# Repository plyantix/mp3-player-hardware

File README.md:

# MiniMusicBox

An open source, RP2350 based MP3 player, with LiPo battery charging, USB-C, MicroSD storage, high fidelity analog audio, and a black & white LCD screen.

Although this version of the project will work, I would not recommend building it, as it has a design flaw leading to high idle battery consumption. This will be fixed in a future revision.

This board was designed with the manufacturing tolerances of [JLCPCB](https://jlcpcb.com/) in mind.

(Incomplete) firmware [here](https://github.com/plyantix/mp3-project-software).

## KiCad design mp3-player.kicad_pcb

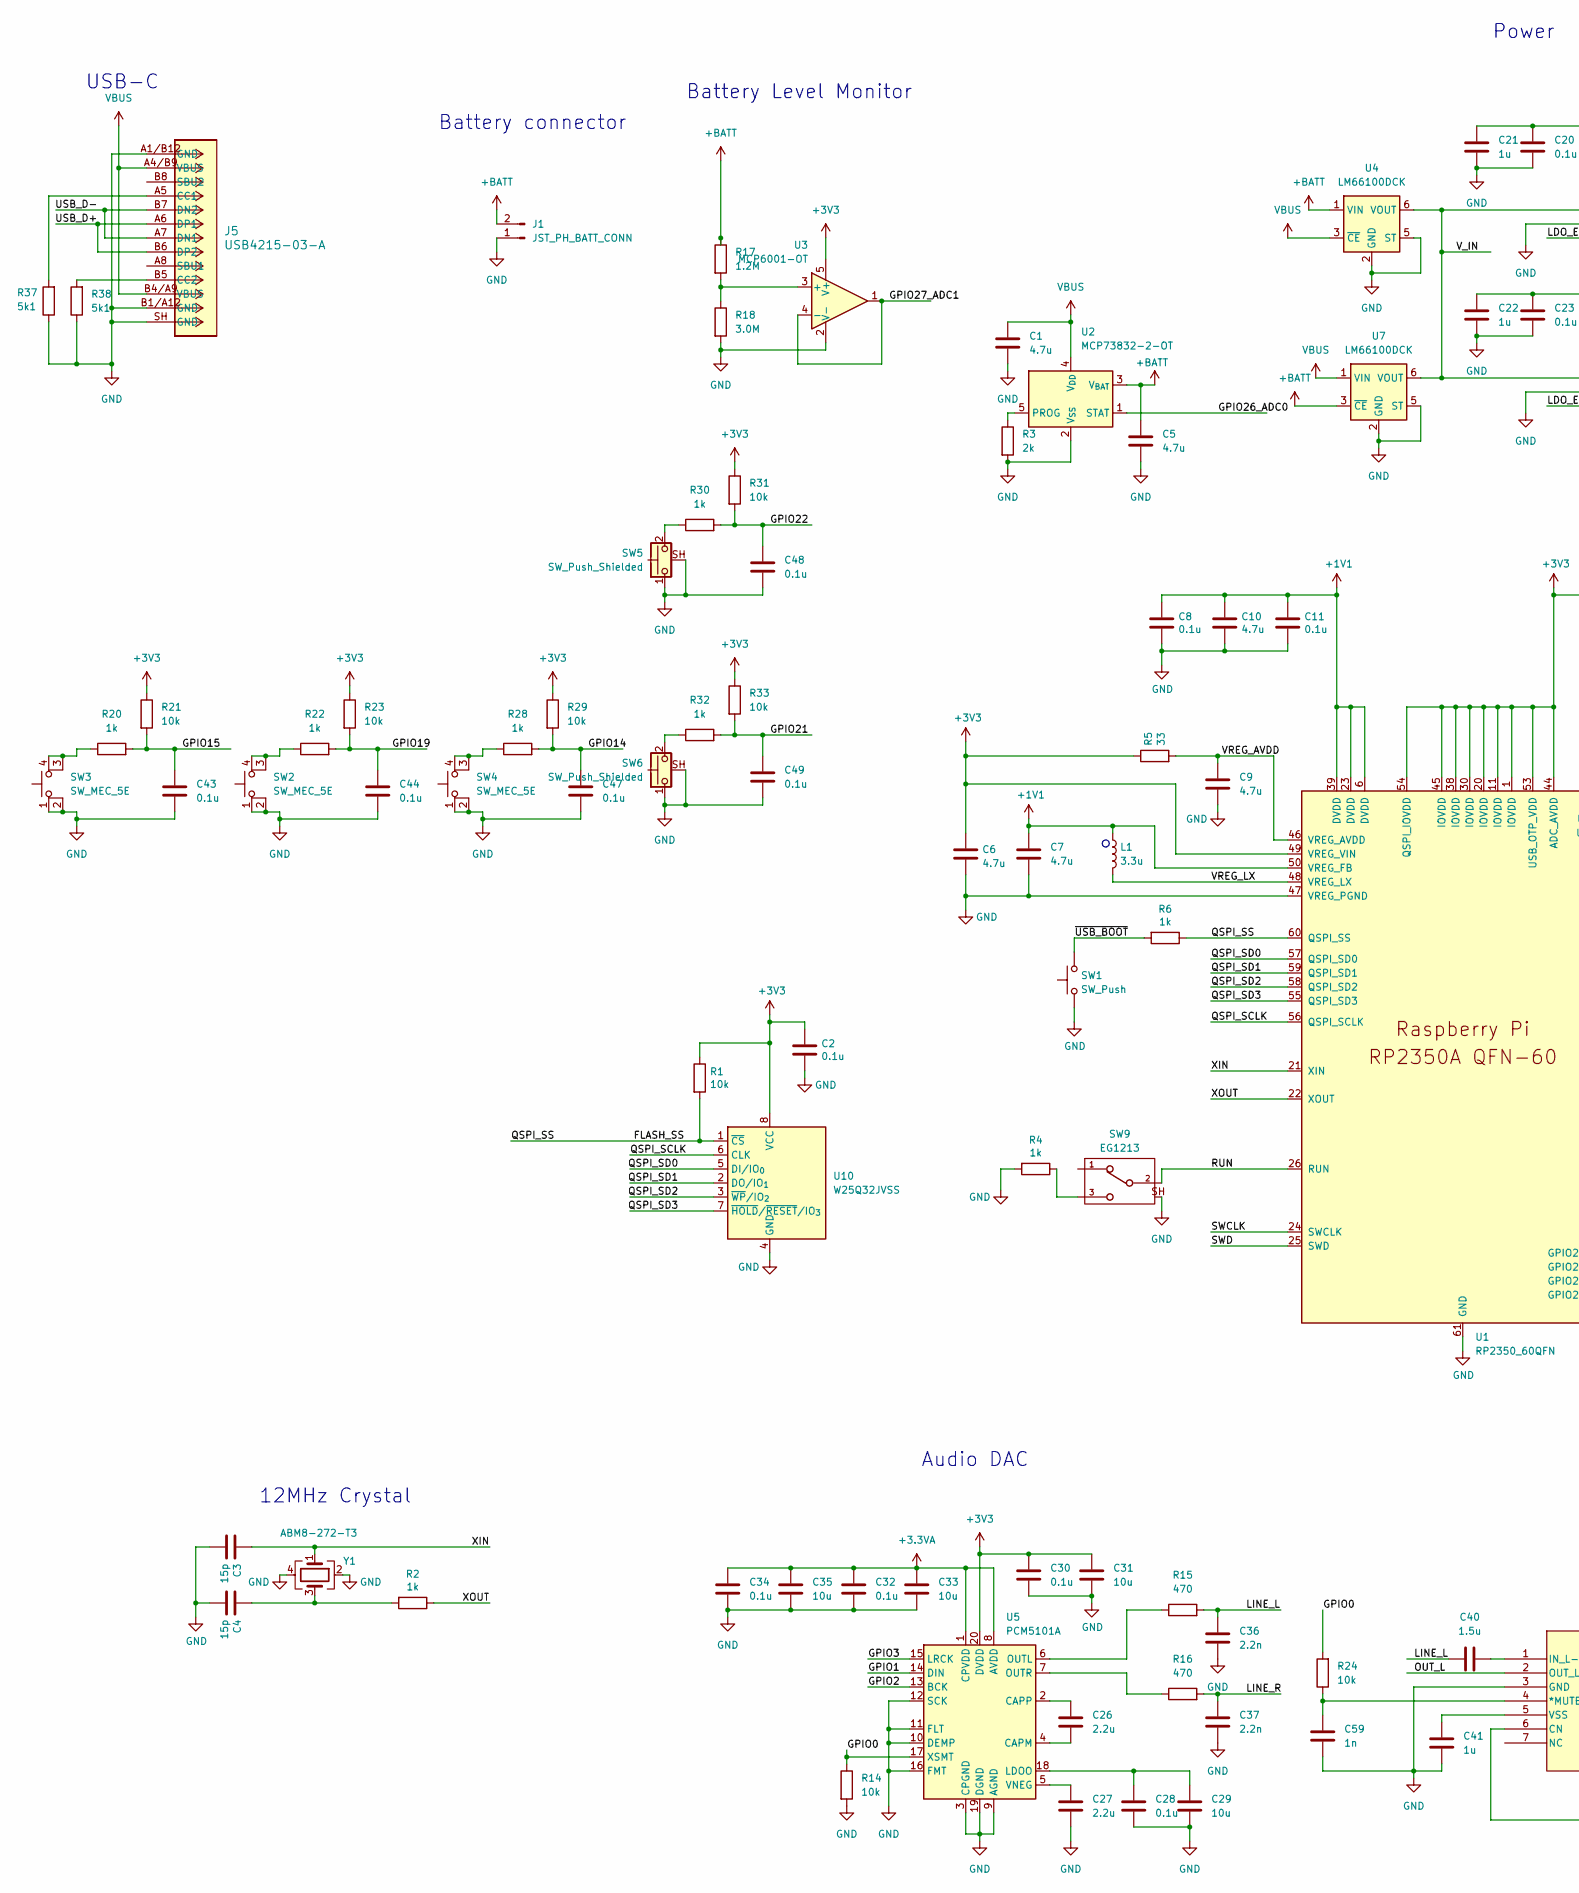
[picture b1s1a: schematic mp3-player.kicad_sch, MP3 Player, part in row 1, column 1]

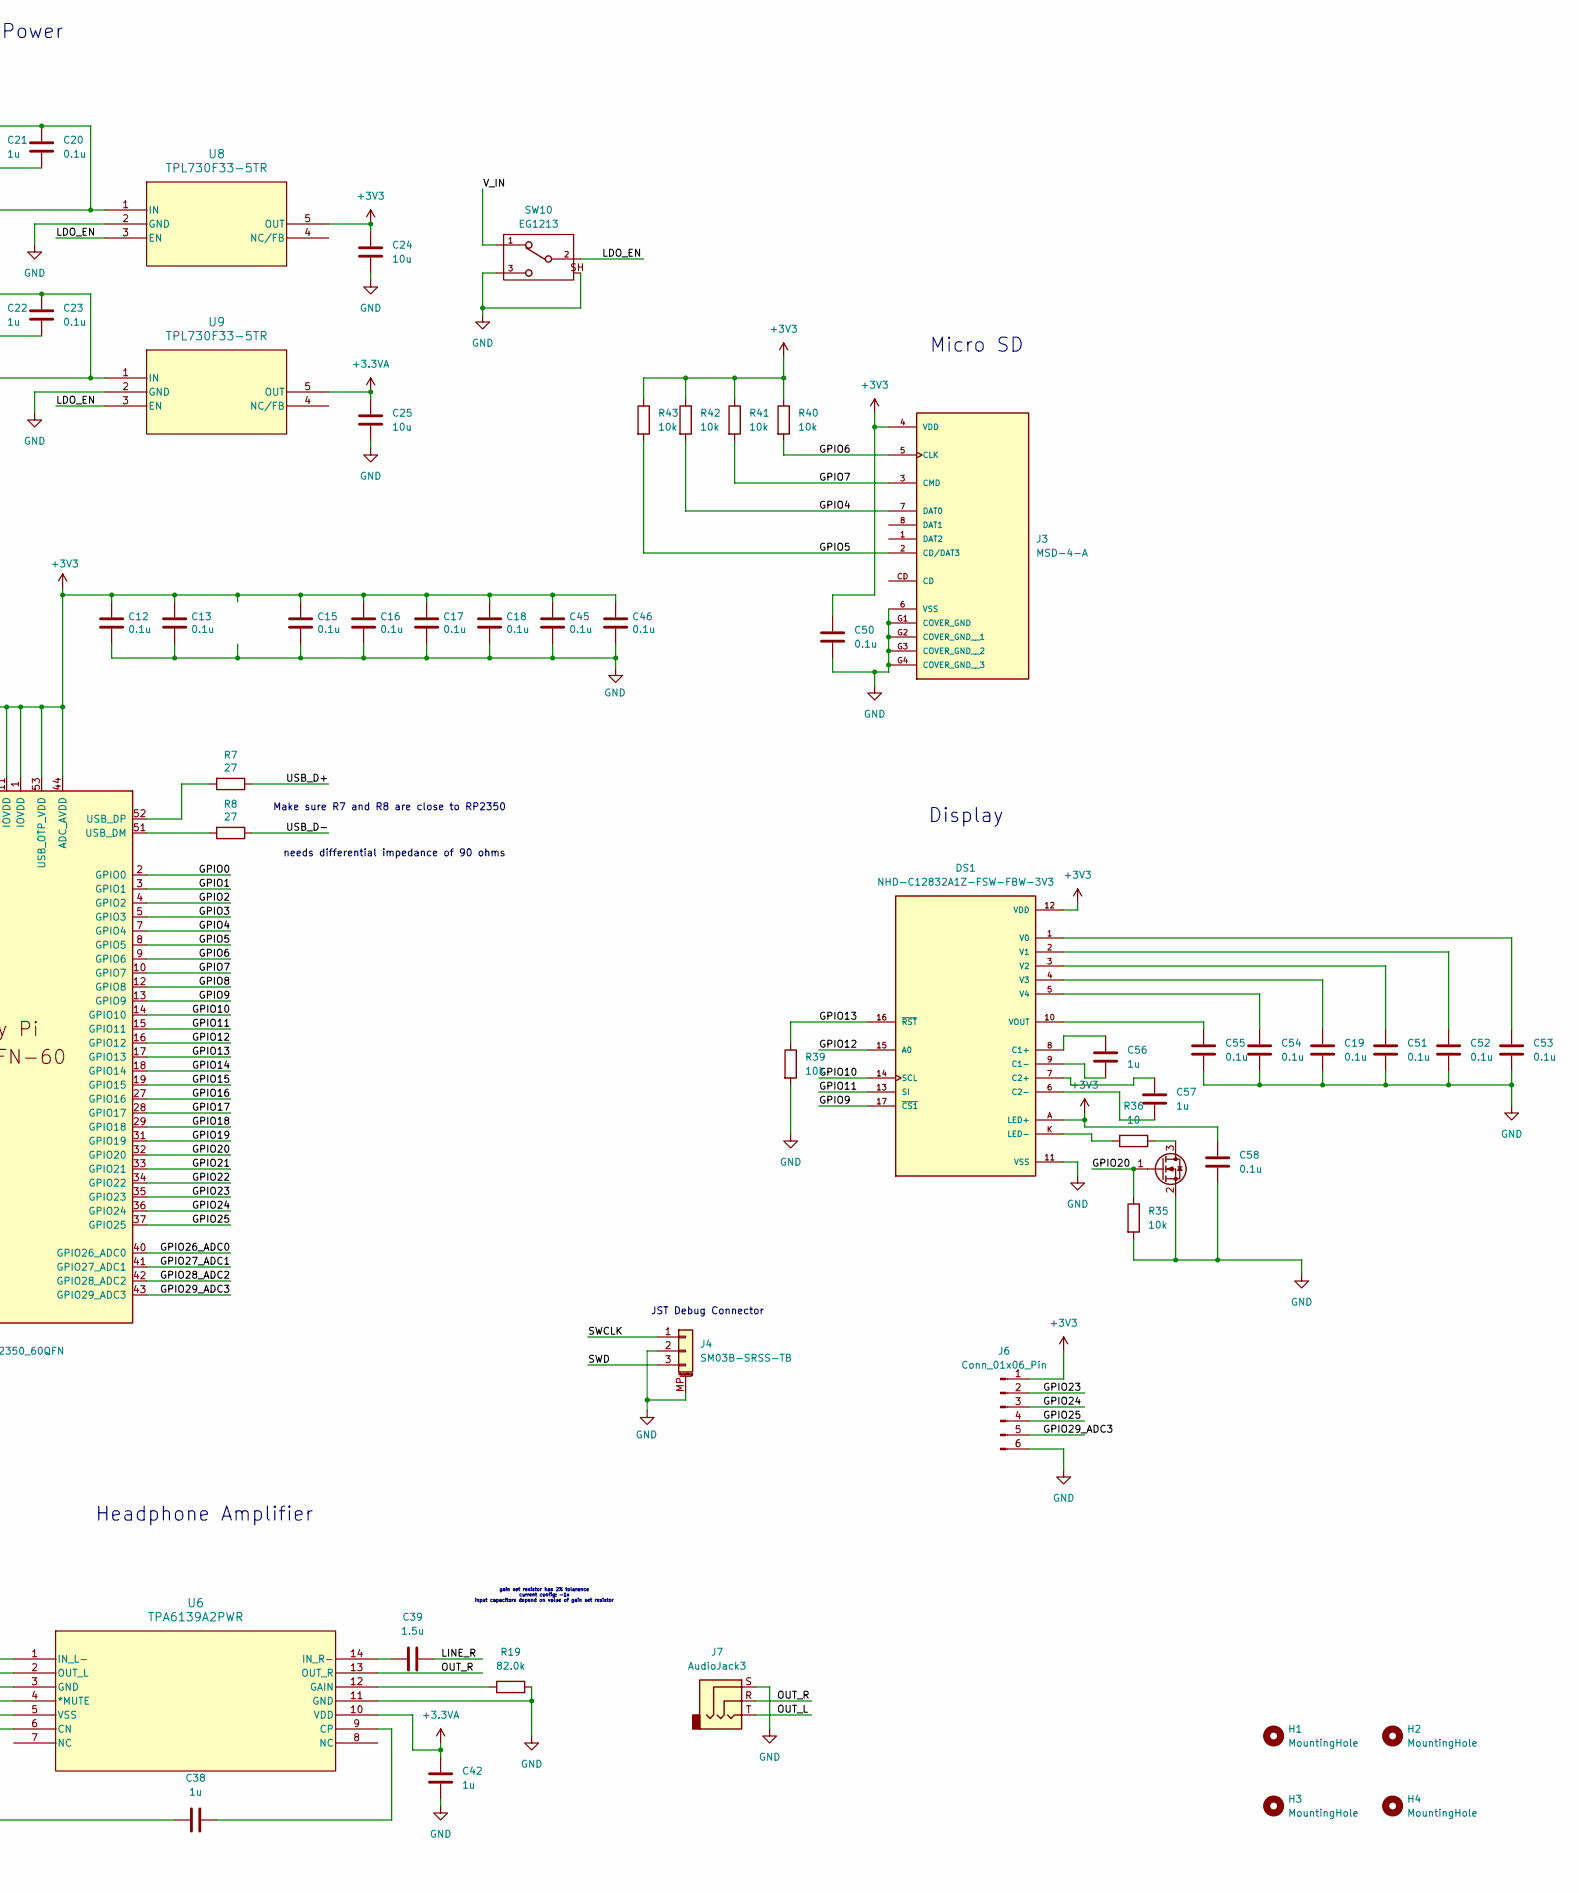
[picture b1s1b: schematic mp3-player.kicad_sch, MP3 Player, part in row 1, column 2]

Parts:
C1, C5, C9, C10: 4.7u; C_0402_1005Metric_NoSilk
C2, C8, C11, C12, C13, C15, C16, C17, C18, C19, C20, C23, C28, C30, C32, C34, C43, C44, C45, C46, C47, C48, C49, C50, C51, C52, C53, C54, C55, C58: 0.1u; C_0402_1005Metric_NoSilk
C3, C4: 15p; C_0402_1005Metric_NoSilk
C6, C7: 4.7u; C_0402_1005Metric_small_pads
C21, C22, C38, C41, C42, C56, C57: 1u; C_0402_1005Metric_NoSilk
C24, C25, C29, C31, C33, C35: 10u; C_0402_1005Metric_NoSilk
C26, C27: 2.2u; C_0402_1005Metric_NoSilk
C36, C37: 2.2n; C_0402_1005Metric_NoSilk
C39, C40: 1.5u; C_0402_1005Metric_NoSilk
C59: 1n; C_0402_1005Metric_NoSilk
DS1: NHD-C12832A1Z-FSW-FBW-3V3; LCD_NHD-C12832A1Z-FSW-FBW-3V3; PARTREV 7
H1, H2, H3, H4: MountingHole; MountingHole_3.2mm_M3
J1: JST_PH_BATT_CONN; JST_PH_S2B-PH-K_1x02_P2.00mm_Horizontal
J3: MSD-4-A; CUI_MSD-4-A; PARTREV 1.0
J4: SM03B-SRSS-TB; JST_SH_SM03B-SRSS-TB_1x03-1MP_P1.00mm_Horizontal
J5: USB4215-03-A; CONN_8p94X6p5X3p16_12L_GCC
J6: Conn_01x06_Pin; PinHeader_1x06_P1.00mm_Vertical
J7: AudioJack3; KYCON_STX-3000
L1: 3.3u; L_pol_2016
Q2: 2N7002; SOT-23
R1, R14, R21, R23, R24, R29, R31, R33, R35, R39, R40, R41, R42, R43: 10k; R_0402_1005Metric_NoSilk
R2, R4, R6, R20, R22, R28, R30, R32: 1k; R_0402_1005Metric_NoSilk
R3: 2k; R_0402_1005Metric_NoSilk
R5: 33; R_0402_1005Metric_NoSilk
R7, R8: 27; R_0402_1005Metric_NoSilk
R15, R16: 470; R_0402_1005Metric_NoSilk
R17: 1.2M; R_0402_1005Metric_NoSilk
R18: 3.0M; R_0402_1005Metric_NoSilk
R19: 82.0k; R_0402_1005Metric_NoSilk
R36: 10; R_0402_1005Metric_NoSilk
R37, R38: 5k1; R_0402_1005Metric_NoSilk
SW1: SW_Push; SW_Push_1P1T_NO_Vertical_Wuerth_434133025816
SW2, SW3, SW4: SW_MEC_5E; SW4_1825910-B_TEC
SW5, SW6: SW_Push_Shielded; SW2_1825027-A_TEC
SW9, SW10: EG1213; OS102011MA1QN1_CNK
U1: RP2350_60QFN; RP2350-QFN-60-1EP_7x7_P0.4mm_EP3.4x3.4mm_ThermalVias
U2: MCP73832-2-OT; SOT-23-5
U3: MCP6001-OT; SOT-23-5
U4, U7: LM66100DCK; SOT-363_SC-70-6
U5: PCM5101A; TSSOP-20_4.4x6.5mm_P0.65mm
U6: TPA6139A2PWR; PW14
U8, U9: TPL730F33-5TR; SOT23-5-A_TPK
U10: W25Q32JVSS; SOIC-8_5.3x5.3mm_P1.27mm
Y1: ABM8-272-T3; Crystal_SMD_3225-4Pin_3.2x2.5mm

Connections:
+1V1: C7.1, C8.1, C10.1, C11.1, L1.1, U1.6 (DVDD), U1.23 (DVDD), U1.39 (DVDD), U1.50 (VREG_FB)
+3.3VA: C25.1, C32.1, C33.1, C34.1, C35.1, C42.1, U5.1 (CPVDD), U5.8 (AVDD), U6.10 (VDD), U9.5 (OUT)
+3V3: C2.1, C6.1, C12.1, C13.1, C15.1, C16.1, C17.1, C18.1, C24.1, C30.1, C31.1, C45.1, C46.1, C50.1, C58.1, DS1.12 (VDD), DS1.A (LED+), J3.4 (VDD), J6.1, R1.1, R5.1, R21.1, R23.1, R29.1, R31.1, R33.1, R40.1, R41.1, R42.1, R43.1, U1.1 (IOVDD), U1.11 (IOVDD), U1.20 (IOVDD), U1.30 (IOVDD), U1.38 (IOVDD), U1.44 (ADC_AVDD), U1.45 (IOVDD), U1.49 (VREG_VIN), U1.53 (USB_OTP_VDD), U1.54 (QSPI_IOVDD), U3.5 (V+), U5.20 (DVDD), U8.5 (OUT), U10.8 (VCC)
+BATT: C5.1, J1.2, R17.1, U2.3 (V_{BAT}), U4.1 (VIN), U7.3 (~CE)
/FLASH_SS: R1.2, R6.1, U1.60 (QSPI_SS), U10.1 (~CS)
/GPIO0: R14.1, R24.2, U1.2 (GPIO0), U5.17 (XSMT)
/GPIO1: U1.3 (GPIO1), U5.14 (DIN)
/GPIO2: U1.4 (GPIO2), U5.13 (BCK)
/GPIO3: U1.5 (GPIO3), U5.15 (LRCK)
/GPIO4: J3.7 (DAT0), R42.2, U1.7 (GPIO4)
/GPIO5: J3.2 (CD/DAT3), R43.2, U1.8 (GPIO5)
/GPIO6: J3.5 (CLK), R40.2, U1.9 (GPIO6)
/GPIO7: J3.3 (CMD), R41.2, U1.10 (GPIO7)
/GPIO8: U1.12 (GPIO8)
/GPIO9: DS1.17 (~CS1), U1.13 (GPIO9)
/GPIO10: DS1.14 (SCL), U1.14 (GPIO10)
/GPIO11: DS1.13 (SI), U1.15 (GPIO11)
/GPIO12: DS1.15 (A0), U1.16 (GPIO12)
/GPIO13: DS1.16 (~RST), R39.1, U1.17 (GPIO13)
/GPIO14: C47.1, R28.2, R29.2, U1.18 (GPIO14)
/GPIO15: C43.1, R20.2, R21.2, U1.19 (GPIO15)
/GPIO16: U1.27 (GPIO16)
/GPIO17: U1.28 (GPIO17)
/GPIO18: U1.29 (GPIO18)
/GPIO19: C44.1, R22.2, R23.2, U1.31 (GPIO19)
/GPIO20: Q2.1 (G), R35.1, U1.32 (GPIO20)
/GPIO21: C49.1, R32.2, R33.2, U1.33 (GPIO21)
/GPIO22: C48.1, R30.2, R31.2, U1.34 (GPIO22)
/GPIO23: J6.2, U1.35 (GPIO23)
/GPIO24: J6.3, U1.36 (GPIO24)
/GPIO25: J6.4, U1.37 (GPIO25)
/GPIO26_ADC0: U1.40 (GPIO26_ADC0), U2.1 (STAT)
/GPIO27_ADC1: U1.41 (GPIO27_ADC1), U3.1, U3.4 (-)
/GPIO28_ADC2: U1.42 (GPIO28_ADC2)
/GPIO29_ADC3: J6.5, U1.43 (GPIO29_ADC3)
/LINE_L: C36.1, C40.1, R15.2
/LINE_R: C37.1, C39.2, R16.2
/OUT_L: J7.T, U6.2 (OUT_L)
/OUT_R: J7.R, U6.13 (OUT_R)
/QSPI_SCLK: U1.56 (QSPI_SCLK), U10.6 (CLK)
/QSPI_SD0: U1.57 (QSPI_SD0), U10.5 (DI/IO_{0})
/QSPI_SD1: U1.59 (QSPI_SD1), U10.2 (DO/IO_{1})
/QSPI_SD2: U1.58 (QSPI_SD2), U10.3 (~WP/IO_{2})
/QSPI_SD3: U1.55 (QSPI_SD3), U10.7 (~HOLD/~RESET/IO_{3})
/RUN: SW9.2, U1.26 (RUN)
/SWCLK: J4.1, U1.24 (SWCLK); also elsewhere on the board
/SWD: J4.3, U1.25 (SWD); also elsewhere on the board
/USB_D+: J5.A6 (DP1), J5.B6 (DP2), R7.1
/USB_D-: J5.A7 (DN1), J5.B7 (DN2), R8.1
/VREG_AVDD: C9.1, R5.2, U1.46 (VREG_AVDD)
/VREG_LX: L1.2, U1.48 (VREG_LX)
/XIN: C3.1, U1.21 (XIN), Y1.1
/XOUT: R2.1, U1.22 (XOUT)
/~USB_BOOT: R6.2, SW1.2; also elsewhere on the board
GND: C1.2, C2.2, C3.2, C4.2, C5.2, C6.2, C7.2, C8.2, C9.2, C10.2, C11.2, C12.2, C13.2, C15.2, C16.2, C17.2, C18.2, C19.2, C20.2, C21.2, C22.2, C23.2, C24.2, C25.2, C27.2, C28.2, C29.2, C30.2, C31.2, C32.2, C33.2, C34.2, C35.2, C36.2, C37.2, C41.1, C42.2, C43.2, C44.2, C45.2, C46.2, C47.2, C48.2, C49.2, C50.2, C51.2, C52.2, C53.2, C54.2, C55.2, C58.2, C59.1, DS1.11 (VSS), J1.1, J3.6 (VSS), J3.G1 (COVER_GND), J3.G2 (COVER_GND__1), J3.G3 (COVER_GND__2), J3.G4 (COVER_GND__3), J4.2, J4.MP (MountPin), J5.A1/B12 (GND), J5.B1/A12 (GND), J5.SH (GND), J6.6, J7.S, Q2.2 (S), R3.2, R4.2, R14.2, R18.2, R19.2, R35.2, R37.1, R38.1, R39.2, SW1.1, SW2.1, SW2.2, SW3.1, SW3.2, SW4.1, SW4.2, SW5.1, SW5.SH (B), SW6.1, SW6.SH (B), SW9.SH, SW10.3, SW10.SH, U1.47 (VREG_PGND), U1.61 (GND), U2.2 (V_{SS}), U3.2 (V-), U4.2 (GND), U4.5 (ST), U5.3 (CPGND), U5.9 (AGND), U5.10 (DEMP), U5.11 (FLT), U5.12 (SCK), U5.16 (FMT), U5.19 (DGND), U6.3 (GND), U6.11 (GND), U7.2 (GND), U7.5 (ST), U8.2 (GND), U9.2 (GND), U10.4 (GND), Y1.2, Y1.4; also elsewhere on the board
unnamed: C4.1, R2.2, Y1.3
unnamed: C56.2, DS1.8 (C1+)
unnamed: C56.1, DS1.9 (C1-)
unnamed: C57.2, DS1.7 (C2+)
unnamed: C57.1, DS1.6 (C2-)
unnamed: DS1.K (LED-), R36.2
unnamed: C53.1, DS1.1 (V0)
unnamed: C52.1, DS1.2 (V1)
unnamed: C51.1, DS1.3 (V2)
unnamed: C19.1, DS1.4 (V3)
unnamed: C54.1, DS1.5 (V4)
unnamed: C55.1, DS1.10 (VOUT)
unnamed: J5.A5 (CC1), R37.2
unnamed: J5.B5 (CC2), R38.2
unnamed: Q2.3 (D), R36.1
unnamed: R4.1, SW9.3
unnamed: R30.1, SW5.2
unnamed: R32.1, SW6.2
unnamed: R22.1, SW2.3 (K), SW2.4 (A)
unnamed: R20.1, SW3.3 (K), SW3.4 (A)
unnamed: R28.1, SW4.3 (K), SW4.4 (A)
unnamed: R8.2, U1.51 (USB_DM)
unnamed: R7.2, U1.52 (USB_DP)
unnamed: R3.1, U2.5 (PROG)
unnamed: R17.2, R18.1, U3.3 (+)
unnamed: C26.2, U5.4 (CAPM)
unnamed: C26.1, U5.2 (CAPP)
unnamed: C28.1, C29.1, U5.18 (LDOO)
unnamed: R15.1, U5.6 (OUTL)
unnamed: R16.1, U5.7 (OUTR)
unnamed: C27.1, U5.5 (VNEG)
unnamed: C59.2, R24.1, U6.4 (*MUTE)
unnamed: C38.2, U6.6 (CN)
unnamed: C38.1, U6.9 (CP)
unnamed: R19.1, U6.12 (GAIN)
unnamed: C40.2, U6.1 (IN_L-)
unnamed: C39.1, U6.14 (IN_R-)
unnamed: C41.2, U6.5 (VSS)
VBUS: C1.1, J5.A4/B9 (VBUS), J5.B4/A9 (VBUS), U2.4 (V_{DD}), U4.3 (~CE), U7.1 (VIN)

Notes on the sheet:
USB-C
Battery connector
Micro SD
Power
12MHz Crystal
needs differential impedance of 90 ohms
Battery Level Monitor
JST Debug Connector
Audio DAC
gain set resistor has 2% tolarance current config: -1x input capacitors depend on value of gain set resistor
Make sure R7 and R8 are close to RP2350
Display
Headphone Amplifier

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
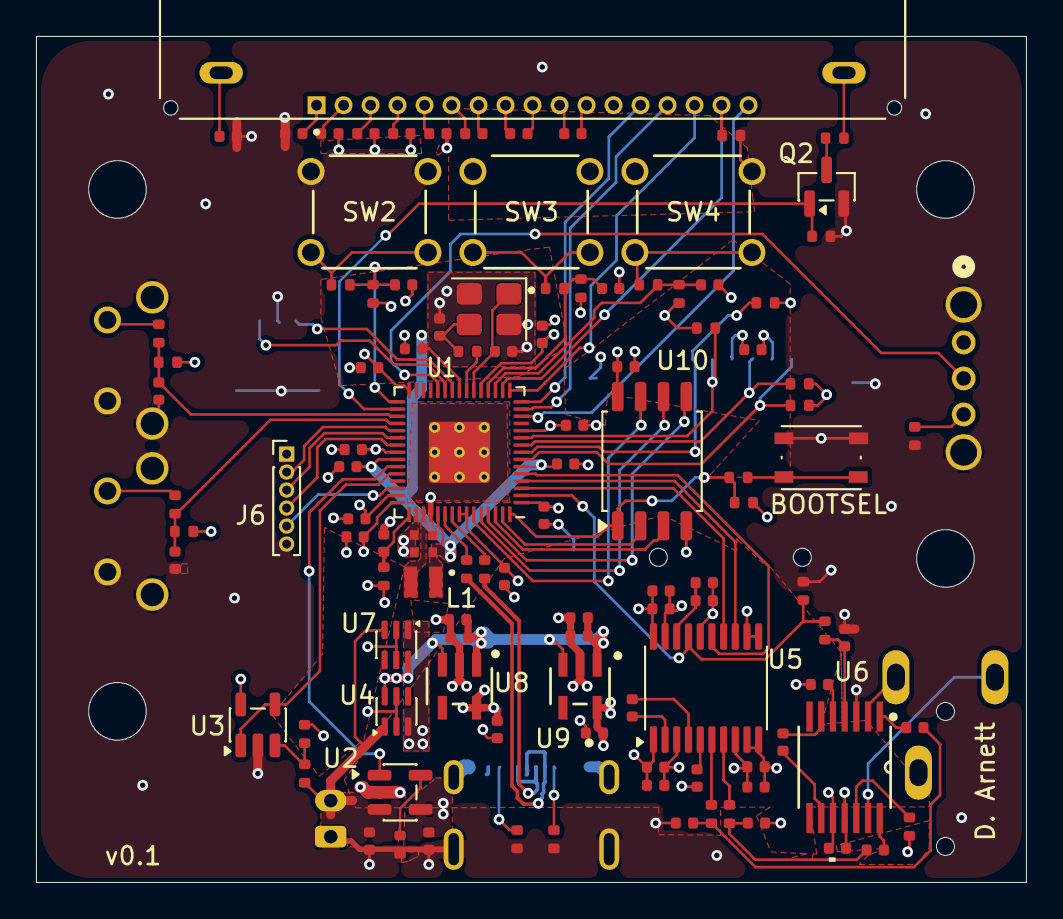
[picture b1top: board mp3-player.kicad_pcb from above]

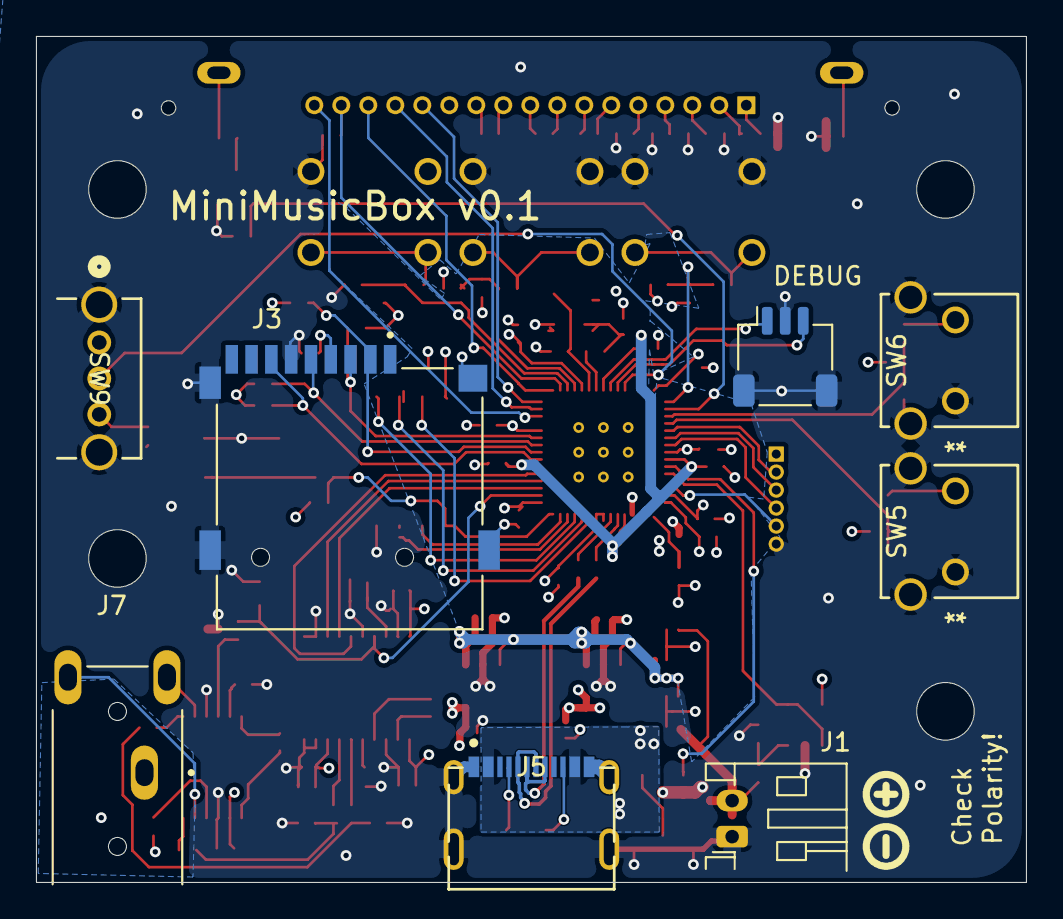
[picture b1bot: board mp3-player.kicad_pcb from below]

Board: 4 copper layers, 55.0 x 47.0 mm, 123 parts (8 on the bottom side), 90 nets.

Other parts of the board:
BOOTSEL: SW_Push; SW_Push_1P1T_NO_Vertical_Wuerth_434133025816
DEBUG: SM03B-SRSS-TB; JST_SH_SM03B-SRSS-TB_1x03-1MP_P1.00mm_Horizontal

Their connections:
/SWCLK: DEBUG.1; also elsewhere on the board
/SWD: DEBUG.3; also elsewhere on the board
/~USB_BOOT: BOOTSEL.2; also elsewhere on the board
GND: BOOTSEL.1, DEBUG.2, DEBUG.MP (MountPin); also elsewhere on the board

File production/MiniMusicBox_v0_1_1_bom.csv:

Designator,Footprint,Quantity,Value,LCSC Part #
BOOTSEL,SW_Push_1P1T_NO_Vertical_Wuerth_434133025816,1,SW_Push,
"C1, C10, C5, C6, C7, C9",0402,6,4.7u,
"C11, C12, C13, C15, C16, C17, C18, C19, C2, C20, C23, C28, C30, C32, C34, C43, C44, C45, C46, C47, C48, C49, C50, C51, C52, C53, C54, C55, C58, C8",0402,30,0.1u,
"C21, C22, C38, C41, C42, C56, C57",0402,7,1u,
"C24, C25, C29, C31, C33, C35",0402,6,10u,
"C26, C27",0402,2,2.2u,
"C3, C4",0402,2,15p,
"C36, C37",0402,2,2.2n,
"C39, C40",0402,2,1.5u,
C59,0402,1,1n,
J1,JST_PH_S2B-PH-K_1x02_P2.00mm_Horizontal,1,JST_PH_BATT_CONN,
L1,L_pol_2016,1,3.3u,
Q2,SOT-23,1,2N7002,
"R1, R14, R21, R23, R24, R29, R31, R33, R35, R39, R40, R41, R42, R43",0402,14,10k,
"R15, R16",0402,2,470,
R17,0402,1,1.2M,
R18,0402,1,3.0M,
R19,0402,1,82.0k,
"R2, R20, R22, R28, R30, R32, R4, R6",0402,8,1k,
R3,0402,1,2k,
R36,0402,1,10,
"R37, R38",0402,2,5k1,
R5,0402,1,33,
"R7, R8",0402,2,27,
U1,RP2350-QFN-60-1EP_7x7_P0.4mm_EP3.4x3.4mm_ThermalVias,1,RP2350_60QFN,
U10,SOIC-8_5.3x5.3mm_P1.27mm,1,W25Q32JVSS,
U2,SOT-23-5,1,MCP73832-2-OT,
U3,SOT-23-5,1,MCP6001-OT,
"U4, U7",SOT-363_SC-70-6,2,LM66100DCK,
U5,TSSOP-20_4.4x6.5mm_P0.65mm,1,PCM5101A,
U6,PW14,1,TPA6139A2PWR,
"U8, U9",SOT23-5-A_TPK,2,TPL730F33-5TR,
Y1,Crystal_SMD_3225-4Pin_3.2x2.5mm,1,ABM8-272-T3,

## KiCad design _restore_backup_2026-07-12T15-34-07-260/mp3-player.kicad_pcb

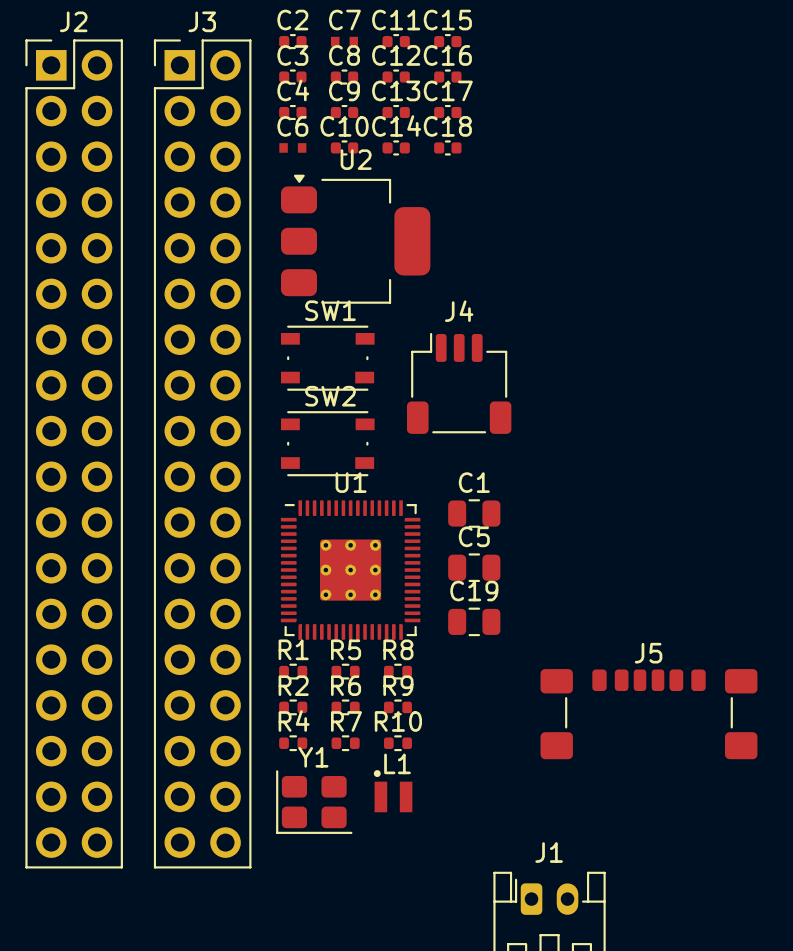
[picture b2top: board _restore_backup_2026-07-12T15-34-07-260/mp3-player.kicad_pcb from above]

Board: 2 copper layers, 39 parts (0 on the bottom side), 48 nets, no tracks yet.

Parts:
C1, C5, C19: 10u; C_0805_2012Metric
C2, C8, C11, C12, C13, C14, C15, C16, C17, C18: 100n; C_0402_1005Metric
C3, C4: 15p; C_0402_1005Metric
C6, C7: 4.7u; C_0402_1005Metric_small_pads
C9, C10: 4.7u; C_0402_1005Metric
J1: Conn_01x02; JST_PH_S2B-PH-K_1x02_P2.00mm_Horizontal
J2, J3: Conn_02x18_Odd_Even; PinHeader_2x18_P2.54mm_Vertical
J4: SM03B-SRSS-TB; JST_SH_SM03B-SRSS-TB_1x03-1MP_P1.00mm_Horizontal
J5: USB_C_Receptacle_USB2.0_14P; USB_C_Receptacle_GCT_USB4135-GF-A_6P_TopMnt_Horizontal
L1: 3.3u; L_pol_2016
R1, R9: DNF; R_0402_1005Metric
R2, R4, R6: 1k; R_0402_1005Metric
R5: 33; R_0402_1005Metric
R7, R8: 27; R_0402_1005Metric
R10: 0; R_0402_1005Metric
SW1, SW2: SW_Push; SW_Push_1P1T_NO_Vertical_Wuerth_434133025816
U1: RP2350_60QFN; RP2350-QFN-60-1EP_7x7_P0.4mm_EP3.4x3.4mm_ThermalVias
U2: NCP1117-3.3_SOT223; SOT-223-3_TabPin2
Y1: ABM8-272-T3; Crystal_SMD_3225-4Pin_3.2x2.5mm

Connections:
+1V1: C7.1, C8.1, C10.1, C11.1, L1.1, U1.6 (DVDD), U1.23 (DVDD), U1.39 (DVDD), U1.50 (VREG_FB)
+3V3: C2.1, C5.1, C6.1, C12.1, C13.1, C14.1, C15.1, C16.1, C17.1, C18.1, C19.1, J2.2, R1.1, R5.1, U1.1 (IOVDD), U1.11 (IOVDD), U1.20 (IOVDD), U1.30 (IOVDD), U1.38 (IOVDD), U1.44 (ADC_AVDD), U1.45 (IOVDD), U1.49 (VREG_VIN), U1.53 (USB_OTP_VDD), U1.54 (QSPI_IOVDD), U2.2 (VO)
/FLASH_SS: R1.2, R9.2, R10.2
/GPIO0: J2.4, R9.1, U1.2 (GPIO0)
/GPIO1: J2.6, U1.3 (GPIO1)
/GPIO2: J2.8, U1.4 (GPIO2)
/GPIO3: J2.10, U1.5 (GPIO3)
/GPIO4: J2.12, U1.7 (GPIO4)
/GPIO5: J2.14, U1.8 (GPIO5)
/GPIO6: J2.16, U1.9 (GPIO6)
/GPIO7: J2.18, U1.10 (GPIO7)
/GPIO8: J2.20, U1.12 (GPIO8)
/GPIO9: J2.22, U1.13 (GPIO9)
/GPIO10: J2.24, U1.14 (GPIO10)
/GPIO11: J2.26, U1.15 (GPIO11)
/GPIO12: J2.28, U1.16 (GPIO12)
/GPIO13: J2.30, U1.17 (GPIO13)
/GPIO14: J2.32, U1.18 (GPIO14)
/GPIO15: J2.34, U1.19 (GPIO15)
/GPIO16: J3.27, U1.27 (GPIO16)
/GPIO17: J3.25, U1.28 (GPIO17)
/GPIO18: J3.23, U1.29 (GPIO18)
/GPIO19: J3.21, U1.31 (GPIO19)
/GPIO20: J3.19, U1.32 (GPIO20)
/GPIO21: J3.17, U1.33 (GPIO21)
/GPIO22: J3.15, U1.34 (GPIO22)
/GPIO23: J3.13, U1.35 (GPIO23)
/GPIO24: J3.11, U1.36 (GPIO24)
/GPIO25: J3.9, U1.37 (GPIO25)
/GPIO26_ADC0: J3.7, U1.40 (GPIO26_ADC0)
/GPIO27_ADC1: J3.5, U1.41 (GPIO27_ADC1)
/GPIO28_ADC2: J3.3, U1.42 (GPIO28_ADC2)
/GPIO29_ADC3: J3.1, U1.43 (GPIO29_ADC3)
/QSPI_SS: R6.1, R10.1, U1.60 (QSPI_SS)
/RUN: J3.29, SW2.2, U1.26 (RUN)
/SWCLK: J3.33, J4.1, U1.24 (SWCLK)
/SWD: J3.31, J4.3, U1.25 (SWD)
/VREG_AVDD: C9.1, R5.2, U1.46 (VREG_AVDD)
/VREG_LX: L1.2, U1.48 (VREG_LX)
/XIN: C3.1, U1.21 (XIN), Y1.1
/XOUT: R2.1, U1.22 (XOUT)
/~USB_BOOT: R6.2, SW1.2
GND: C1.2, C2.2, C3.2, C4.2, C5.2, C6.2, C7.2, C8.2, C9.2, C10.2, C11.2, C12.2, C13.2, C14.2, C15.2, C16.2, C17.2, C18.2, C19.2, J2.1, J2.3, J2.5, J2.7, J2.9, J2.11, J2.13, J2.15, J2.17, J2.19, J2.21, J2.23, J2.25, J2.27, J2.29, J2.31, J2.33, J2.35, J2.36, J3.2, J3.4, J3.6, J3.8, J3.10, J3.12, J3.14, J3.16, J3.18, J3.20, J3.22, J3.24, J3.26, J3.28, J3.30, J3.32, J3.34, J3.35, J3.36, J4.2, J4.MP (MountPin), J5.A12 (GND), J5.B12 (GND), J5.SH (SHIELD), R4.2, SW1.1, U1.47 (VREG_PGND), U1.61 (GND), U2.1 (GND), Y1.2, Y1.4
unnamed: C4.1, R2.2, Y1.3
unnamed: R4.1, SW2.1
unnamed: R8.2, U1.51 (USB_DM)
unnamed: R7.2, U1.52 (USB_DP)
VBUS: C1.1, J5.A9 (VBUS), J5.B9 (VBUS), U2.3 (VI)
